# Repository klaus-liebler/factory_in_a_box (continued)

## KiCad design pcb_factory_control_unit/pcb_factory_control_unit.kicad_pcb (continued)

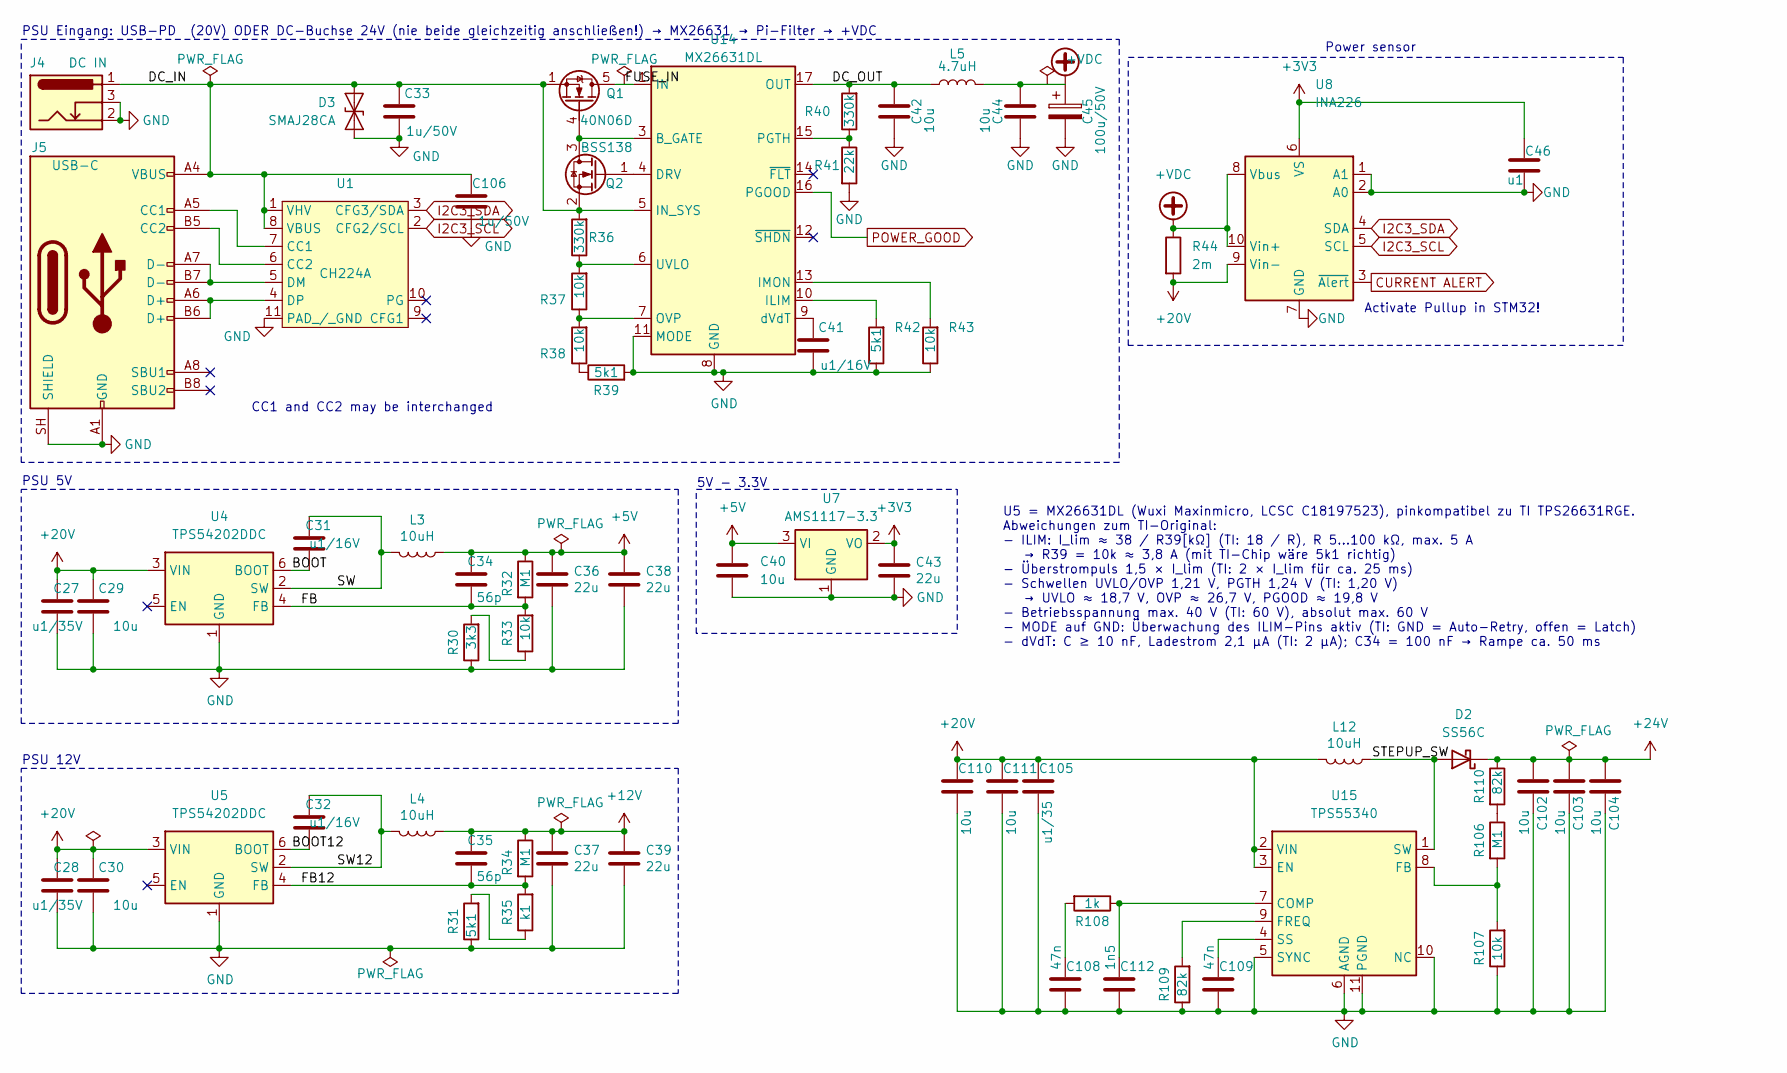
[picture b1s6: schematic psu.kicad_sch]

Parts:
C27, C28: u1/35V; C_0805_2012Metric; MPN CC0805KRX7R9BB104; LCSC C49678
C29, C30, C40, C110, C111: 10u; C_0805_2012Metric; MPN CGA0805X5R106K500MT; LCSC C6119889
C31, C32, C41: u1/16V; C_0402_1005Metric; MPN CL05B104KO5NNNC; LCSC C1525
C33, C106: 1u/50V; C_0805_2012Metric; MPN CL21B105KBFNNNE; LCSC C28323
C34, C35: 56p; C_0402_1005Metric; MPN CC0402JRNPO9BN560; LCSC C107007
C36, C37, C38, C39, C43: 22u; C_0805_2012Metric; MPN CL21A226MAQNNNE; LCSC C45783
C42, C44, C102, C103, C104: 10u; C_1210_3225Metric; MPN GRM32ER71H106KA12L; LCSC C77102
C45: 100u/50V; CP_Elec_8x10; MPN EEE-FK1H101P; LCSC C178548
C46: u1; C_0402_1005Metric; MPN CL05B104KO5NNNC; LCSC C1525
C105: u1/35; C_0805_2012Metric; MPN CC0805KRX7R9BB104; LCSC C49678
C108, C109: 47n; C_0402_1005Metric; MPN CL05B473KO5NNNC; LCSC C307434
C112: 1n5; C_0402_1005Metric; MPN CL05B152KB5NNNC; LCSC C23967
D2: SS56C; D_SMC; LCSC C24138
D3: SMAJ28CA; D_SMA; MPN SMAJ28CA; LCSC C19077546
J4: DC IN; BarrelJack_Horizontal; MPN DC-005 2.0
J5: USB-C; USB_C_Receptacle_HRO_TYPE-C-31-M-12_smaller; MPN TYPE-C-31-M-12; LCSC C165948
L3, L4, L12: 10uH; L_Abracon_ASPI-0630LR; MPN FXL0650-100-M; LCSC C475521
L5: 4.7uH; L_Bourns_SRP1245A; LCSC C54620181
Q1: 40N06D; VSON-8_3.3x3.3mm_P0.65mm_NexFET; MPN 40N06D; LCSC C7543836
Q2: BSS138; SOT-23; MPN BSS138LT1G; LCSC C82045
R30: 3k3; R_0402_1005Metric; MPN 0402WGF3301TCE; LCSC C25890
R31, R39, R42: 5k1; R_0402_1005Metric; MPN 0402WGF5101TCE; LCSC C25905
R32, R34, R106: M1; R_0402_1005Metric; MPN 0402WGF1003TCE; LCSC C25741
R33, R37, R38, R43, R107: 10k; R_0402_1005Metric; MPN 0402WGF1002TCE; LCSC C25744
R35: k1; R_0402_1005Metric; MPN 0402WGF1000TCE; LCSC C25076
R36, R40: 330k; R_0402_1005Metric; MPN 0402WGF3303TCE; LCSC C25778
R41: 22k; R_0402_1005Metric; MPN 0402WGF2202TCE; LCSC C25768
R44: 2m; R_1206_3216Metric; LCSC C844294
R108: 1k; R_0402_1005Metric; MPN 0402WGF1001TCE; LCSC C11702
R109, R110: 82k; R_0402_1005Metric; MPN 0402WGF8202TCE; LCSC C4142
U1: CH224A; Texas_DSQ0010A_WSON-10-1EP_2x2mm_P0.4mm_EP0.9x1.5mm_Thermal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; LCSC C42459160
U4, U5: TPS54202DDC; SOT-23-6; MPN TPS54202DDCR; LCSC C191884
U7: AMS1117-3.3; SOT-223-3_TabPin2; LCSC C6186
U8: INA226; TSSOP-10_3x3mm_P0.5mm; LCSC C49851
U14: MX26631DL; Texas_RGE0024H_VQFN-24-1EP_4x4mm_P0.5mm_EP2.7x2.7mm_Thermal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; MPN MX26631DL; LCSC C18197523
U15: TPS55340; WQFN-16-1EP_3x3mm_P0.5mm_EP1.68x1.68mm_ThermalVias; MPN TPS55340RTER; LCSC C169167

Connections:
+3V3: C43.1, C46.1, U7.2 (VO), U8.6 (VS); also elsewhere on the board
+5V: C34.2, C36.1, C38.1, C40.1, L3.1, R32.1, U7.3 (VI); also elsewhere on the board
+12V: C35.2, C37.1, C39.1, L4.1, R34.1; also elsewhere on the board
+20V: C27.2, C28.2, C29.2, C30.2, C105.2, C110.2, C111.2, L12.2, R44.2, U4.3 (VIN), U5.3 (VIN), U8.9 (Vin-), U15.2 (VIN), U15.3 (EN); also elsewhere on the board
+24V: C102.1, C103.1, C104.1, D2.1 (K), R110.1; also elsewhere on the board
+VDC: C44.1, C45.1, L5.2, R44.1, U8.8 (Vbus), U8.10 (Vin+)
/psu/BOOT: C31.1, U4.6 (BOOT)
/psu/BOOT12: C32.1, U5.6 (BOOT)
/psu/DC_IN: C33.2, C106.2, D3.2 (A2), J4.1, J5.A4 (VBUS), J5.A9 (VBUS), J5.B4 (VBUS), J5.B9 (VBUS), Q1.1 (S), Q1.2 (S), Q1.3 (S), Q2.2 (S), R36.2, U1.1 (VHV), U1.8 (VBUS), U14.5 (IN_SYS)
/psu/DC_OUT: C42.1, L5.1, R40.2, U14.17 (OUT), U14.18 (OUT)
/psu/FB: C34.1, R32.2, R33.2, U4.4 (FB)
/psu/FB12: C35.1, R34.2, R35.2, U5.4 (FB)
/psu/FUSE_IN: Q1.5 (D), U14.1 (IN), U14.2 (IN)
/psu/STEPUP_SW: D2.2 (A), L12.1, U15.1 (SW), U15.15 (SW), U15.16 (SW)
/psu/SW: C31.2, L3.2, U4.2 (SW)
/psu/SW12: C32.2, L4.2, U5.2 (SW)
CURRENT ALERT: U8.3 (~Alert); also elsewhere on the board
GND: C27.1, C28.1, C29.1, C30.1, C33.1, C36.2, C37.2, C38.2, C39.2, C40.2, C41.1, C42.2, C43.2, C44.2, C45.2, C46.2, C102.2, C103.2, C104.2, C105.1, C106.1, C108.1, C109.1, C110.1, C111.1, C112.1, D3.1 (A1), J4.2, J4.3, J5.A1 (GND), J5.A12 (GND), J5.B1 (GND), J5.B12 (GND), J5.SH (SHIELD), R30.1, R31.1, R39.2, R41.2, R42.1, R43.1, R107.1, R109.1, U1.11 (PAD_/_GND), U4.1 (GND), U5.1 (GND), U7.1 (GND), U8.1 (A1), U8.2 (A0), U8.7 (GND), U14.8 (GND), U14.11 (MODE), U14.25 (GND), U15.5 (SYNC), U15.6 (AGND), U15.10 (NC), U15.11 (PGND), U15.12 (PGND), U15.13 (PGND), U15.14 (NC), U15.17 (AGND); also elsewhere on the board
I2C3_SCL: U1.2 (CFG2/SCL), U8.5 (SCL); also elsewhere on the board
I2C3_SDA: U1.3 (CFG3/SDA), U8.4 (SDA); also elsewhere on the board
unnamed: C108.2, R108.2
unnamed: J5.A5 (CC1), U1.7 (CC1)
unnamed: J5.B5 (CC2), U1.6 (CC2)
unnamed: Q1.4 (G), Q2.3 (D), U14.3 (B_GATE)
unnamed: Q2.1 (G), U14.4 (DRV)
unnamed: R30.2, R33.1
unnamed: R31.2, R35.1
unnamed: R38.1, R39.1
unnamed: R106.1, R110.2
unnamed: J5.A7 (D-), J5.B7 (D-), U1.5 (DM)
unnamed: J5.A6 (D+), J5.B6 (D+), U1.4 (DP)
unnamed: R42.2, U14.10 (ILIM)
unnamed: R43.2, U14.13 (IMON)
unnamed: R37.1, R38.2, U14.7 (OVP)
unnamed: R40.1, R41.1, U14.15 (PGTH)
unnamed: R36.1, R37.2, U14.6 (UVLO)
unnamed: C41.2, U14.9 (dVdT)
unnamed: C112.2, R108.1, U15.7 (COMP)
unnamed: R106.2, R107.2, U15.8 (FB)
unnamed: R109.2, U15.9 (FREQ)
unnamed: C109.2, U15.4 (SS)
POWER_GOOD: U14.16 (PGOOD); also elsewhere on the board

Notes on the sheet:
PSU 5V
Power sensor
U5 = MX26631DL (Wuxi Maxinmicro, LCSC C18197523), pinkompatibel zu TI TPS26631RGE. Abweichungen zum TI-Original: - ILIM: I_lim ≈ 38 / R39[kΩ] (TI: 18 / R), R 5…100 kΩ, max. 5 A → R39 = 10k ≈ 3,8 A (mit TI-Chip wäre 5k1 richtig) - Überstrompuls 1,5 × I_lim (TI: 2 × I_lim für ca. 25 ms) - Schwellen U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
PSU Eingang: USB-PD (20V) ODER DC-Buchse 24V (nie beide gleichzeitig anschließen!) → MX26631 → Pi-Filter → +VDC
PSU 12V
Activate Pullup in STM32!
CC1 and CC2 may be interchanged
5V - 3.3V

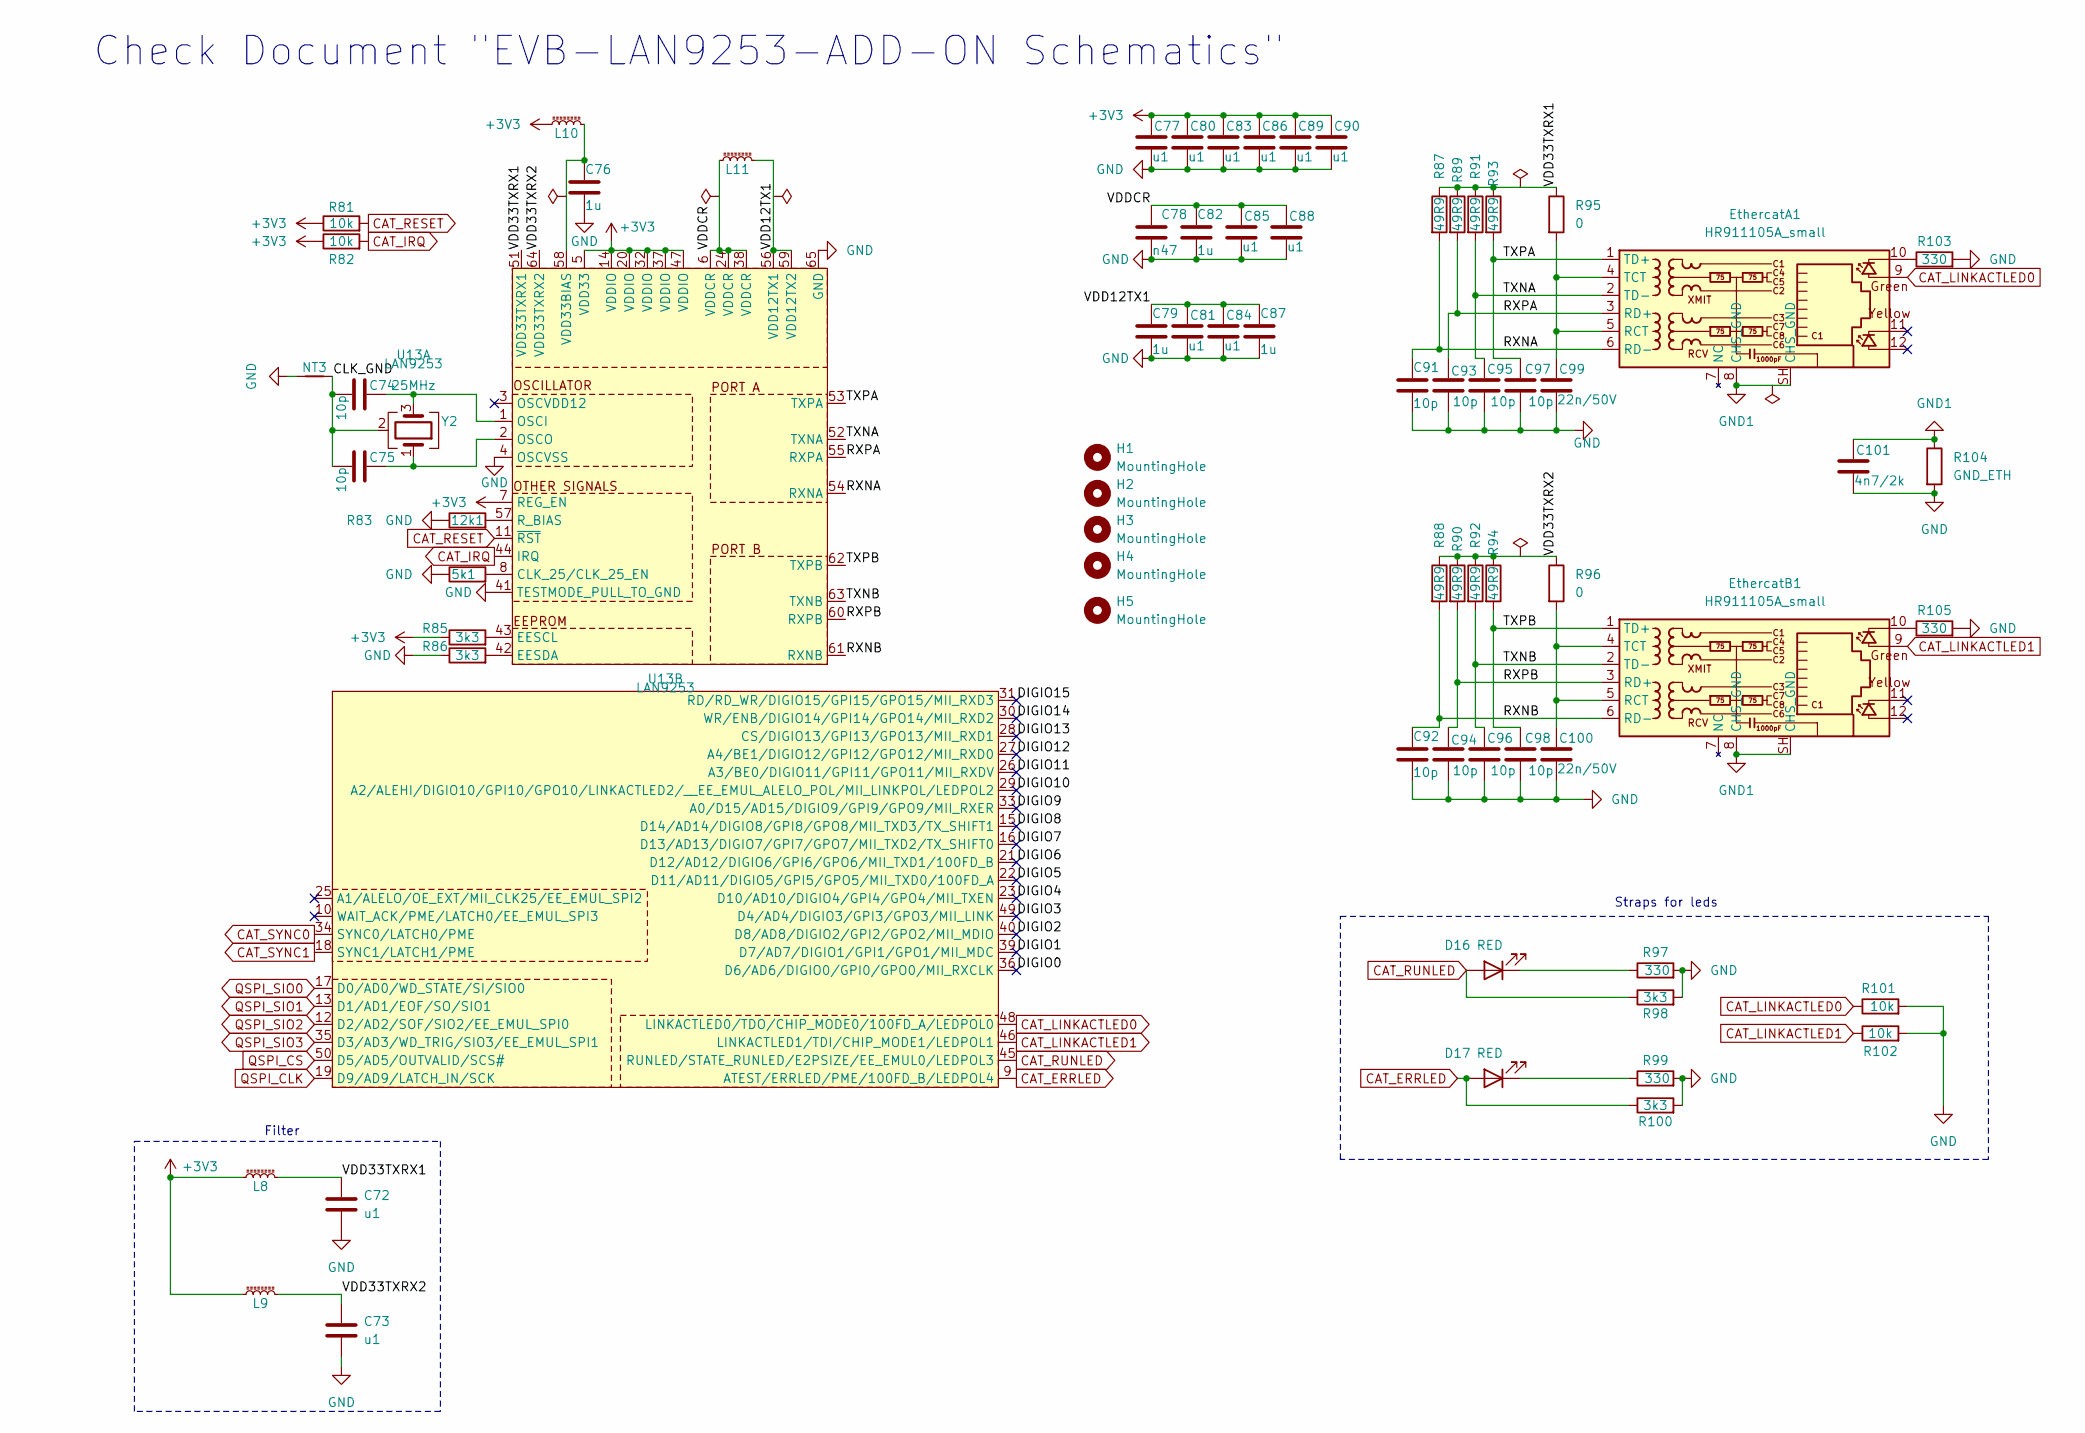
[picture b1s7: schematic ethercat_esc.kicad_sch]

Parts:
C72, C73, C77, C80, C81, C83, C84, C85, C86, C88, C89, C90: u1; C_0402_1005Metric; MPN CL05B104KO5NNNC; LCSC C1525
C74, C75, C91, C92, C93, C94, C95, C96, C97, C98: 10p; C_0402_1005Metric; MPN CC0402JRNPO9BN100; LCSC C106199
C76, C79, C82, C87: 1u; C_0402_1005Metric; MPN CL05A105KA5NQNC; LCSC C52923
C78: n47; C_0402_1005Metric; MPN GRM1555C1H471JA01D; LCSC C76971
C99, C100: 22n/50V; C_0402_1005Metric; MPN 0402B223K500NT; LCSC C1532
C101: 4n7/2k; C_0805_2012Metric_Pad1.18x1.45mm_HandSolder
D16, D17: RED; LED_1206_3216Metric_ReverseMount_Hole1.8x2.4mm; MPN P2-1206RTCS2-0.9T-F; LCSC C2827254
EthercatA1: HR911105A_small; RJ45_HANRUN_HR911105A; LCSC C12074
EthercatB1: HR911105A_small; RJ45_HANRUN_HR911105A; LCSC C12074
H1, H2, H3, H4: MountingHole; MountingHole_4.3mm_M4_DIN965
H5: MountingHole; barrel_jack_positive_polarity
L8, L9, L10, L11: 220R@100M; L_0603_1608Metric; MPN BLM18PG221SN1D; LCSC C80165
NT3: NetTie_2; NetTie-2_SMD_Pad0.5mm
R81, R82, R101, R102: 10k; R_0402_1005Metric; MPN 0402WGF1002TCE; LCSC C25744
R83: 12k1; R_0402_1005Metric; LCSC C25852
R84: 5k1; R_0402_1005Metric; MPN 0402WGF5101TCE; LCSC C25905
R85, R86, R98, R100: 3k3; R_0402_1005Metric; MPN 0402WGF3301TCE; LCSC C25890
R87, R88, R89, R90, R91, R92, R93, R94: 49R9; R_0402_1005Metric; LCSC C25120
R95, R96: 0; R_0805_2012Metric_Pad1.20x1.40mm_HandSolder; MPN 0805W8F0000T5E; LCSC C17477
R97, R99, R103, R105: 330; R_0402_1005Metric; MPN 0402WGF3300TCE; LCSC C25104
R104: GND_ETH; R_0805_2012Metric_Pad1.20x1.40mm_HandSolder
U13: LAN9253; QFN-64-1EP_9x9mm_P0.5mm_EP6x6mm_ThermalVias; MPN LAN9253-I/R4X; LCSC C5745149
Y2: 25MHz; Crystal_SMD_2016-4Pin_2.0x1.6mm; LCSC C19711739

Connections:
+3V3: C77.1, C80.1, C83.1, C86.1, C89.1, C90.1, L8.1, L9.1, L10.1, R81.1, R82.1, R85.1, U13.5 (VDD33), U13.7 (REG_EN), U13.14 (VDDIO), U13.20 (VDDIO), U13.32 (VDDIO), U13.37 (VDDIO), U13.47 (VDDIO); also elsewhere on the board
/EtherCAT/CLK_GND: C74.2, C75.2, NT3.2, Y2.2 (G), Y2.4 (G)
/EtherCAT/DIGIO0: U13.36 (D6/AD6/DIGIO0/GPI0/GPO0/MII_RXCLK)
/EtherCAT/DIGIO1: U13.39 (D7/AD7/DIGIO1/GPI1/GPO1/MII_MDC)
/EtherCAT/DIGIO2: U13.40 (D8/AD8/DIGIO2/GPI2/GPO2/MII_MDIO)
/EtherCAT/DIGIO3: U13.49 (D4/AD4/DIGIO3/GPI3/GPO3/MII_LINK)
/EtherCAT/DIGIO4: U13.23 (D10/AD10/DIGIO4/GPI4/GPO4/MII_TXEN)
/EtherCAT/DIGIO5: U13.22 (D11/AD11/DIGIO5/GPI5/GPO5/MII_TXD0/100F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)
/EtherCAT/DIGIO6: U13.21 (D12/AD12/DIGIO6/GPI6/GPO6/MII_TXD1/100F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)
/EtherCAT/DIGIO7: U13.16 (D13/AD13/DIGIO7/GPI7/GPO7/MII_TXD2/TX_S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)
/EtherCAT/DIGIO8: U13.15 (D14/AD14/DIGIO8/GPI8/GPO8/MII_TXD3/TX_S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)
/EtherCAT/DIGIO9: U13.33 (A0/D15/AD15/DIGIO9/GPI9/GPO9/MII_RXER)
/EtherCAT/DIGIO10: U13.29 (A2/ALEHI/DIGIO10/GPI10/GPO10/LINKACTLED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)
/EtherCAT/DIGIO11: U13.26 (A3/BE0/DIGIO11/GPI11/GPO11/MII_RXDV)
/EtherCAT/DIGIO12: U13.27 (A4/BE1/DIGIO12/GPI12/GPO12/MII_RXD0)
/EtherCAT/DIGIO13: U13.28 (CS/DIGIO13/GPI13/GPO13/MII_RXD1)
/EtherCAT/DIGIO14: U13.30 (WR/ENB/DIGIO14/GPI14/GPO14/MII_RXD2)
/EtherCAT/DIGIO15: U13.31 (RD/RD_WR/DIGIO15/GPI15/GPO15/MII_RXD3)
/EtherCAT/RXNA: C91.1, EthercatA1.6 (RD-), R87.2, U13.54 (RXNA)
/EtherCAT/RXNB: C92.1, EthercatB1.6 (RD-), R88.2, U13.61 (RXNB)
/EtherCAT/RXPA: C93.1, EthercatA1.3 (RD+), R89.2, U13.55 (RXPA)
/EtherCAT/RXPB: C94.1, EthercatB1.3 (RD+), R90.2, U13.60 (RXPB)
/EtherCAT/TXNA: C95.1, EthercatA1.2 (TD-), R91.2, U13.52 (TXNA)
/EtherCAT/TXNB: C96.1, EthercatB1.2 (TD-), R92.2, U13.63 (TXNB)
/EtherCAT/TXPA: C97.1, EthercatA1.1 (TD+), R93.2, U13.53 (TXPA)
/EtherCAT/TXPB: C98.1, EthercatB1.1 (TD+), R94.2, U13.62 (TXPB)
/EtherCAT/VDD12TX1: C79.1, C81.1, C84.1, C87.1, L11.2, U13.56 (VDD12TX1), U13.59 (VDD12TX2)
/EtherCAT/VDD33TXRX1: C72.1, L8.2, R87.1, R89.1, R91.1, R93.1, R95.1, U13.51 (VDD33TXRX1)
/EtherCAT/VDD33TXRX2: C73.1, L9.2, R88.1, R90.1, R92.1, R94.1, R96.1, U13.64 (VDD33TXRX2)
/EtherCAT/VDDCR: C78.1, C82.1, C85.1, C88.1, L11.1, U13.6 (VDDCR), U13.24 (VDDCR), U13.38 (VDDCR)
CAT_ERRLED: D17.2 (A), R100.1, U13.9 (ATEST/ERRLED/PME/100FD_B/LEDPOL4)
CAT_IRQ: R82.2, U13.44 (IRQ); also elsewhere on the board
CAT_LINKACTLED0: EthercatA1.9, R101.1, U13.48 (LINKACTLED0/TDO/CHIP_MODE0/100FD_A/LEDP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)
CAT_LINKACTLED1: EthercatB1.9, R102.1, U13.46 (LINKACTLED1/TDI/CHIP_MODE1/LEDPOL1)
CAT_RESET: R81.2, U13.11 (~RST); also elsewhere on the board
CAT_RUNLED: D16.2 (A), R98.1, U13.45 (RUNLED/STATE_RUNLED/E2PSIZE/EE_EMUL0/LE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)
CAT_SYNC0: U13.34 (SYNC0/LATCH0/PME); also elsewhere on the board
CAT_SYNC1: U13.18 (SYNC1/LATCH1/PME); also elsewhere on the board
GND: C72.2, C73.2, C76.2, C77.2, C78.2, C79.2, C80.2, C81.2, C82.2, C83.2, C84.2, C85.2, C86.2, C87.2, C88.2, C89.2, C90.2, C91.2, C92.2, C93.2, C94.2, C95.2, C96.2, C97.2, C98.2, C99.2, C100.2, C101.2, NT3.1, R83.1, R84.1, R86.1, R97.2, R98.2, R99.2, R100.2, R101.2, R102.2, R103.2, R104.2, R105.2, U13.4 (OSCVSS), U13.41 (TESTMODE_PULL_TO_GND), U13.65 (GND); also elsewhere on the board
GND1: C101.1, EthercatA1.8 (CHS_GND), EthercatA1.SH (CHS_GND), EthercatB1.8 (CHS_GND), EthercatB1.SH (CHS_GND), R104.1; also elsewhere on the board
unnamed: D16.1 (K), R97.1
unnamed: D17.1 (K), R99.1
unnamed: EthercatA1.10, R103.1
unnamed: C99.1, EthercatA1.4 (TCT), EthercatA1.5 (RCT), R95.2
unnamed: EthercatB1.10, R105.1
unnamed: C100.1, EthercatB1.4 (TCT), EthercatB1.5 (RCT), R96.2
unnamed: R84.2, U13.8 (CLK_25/CLK_25_EN)
unnamed: R85.2, U13.43 (EESCL)
unnamed: R86.2, U13.42 (EESDA)
unnamed: C74.1, U13.1 (OSCI), Y2.3
unnamed: C75.1, U13.2 (OSCO), Y2.1
unnamed: R83.2, U13.57 (R_BIAS)
unnamed: C76.1, L10.2, U13.58 (VDD33BIAS)
QSPI_CLK: U13.19 (D9/AD9/LATCH_IN/SCK); also elsewhere on the board
QSPI_CS: U13.50 (D5/AD5/OUTVALID/SCS#); also elsewhere on the board
QSPI_SIO0: U13.17 (D0/AD0/WD_STATE/SI/SIO0); also elsewhere on the board
QSPI_SIO1: U13.13 (D1/AD1/EOF/SO/SIO1); also elsewhere on the board
QSPI_SIO2: U13.12 (D2/AD2/SOF/SIO2/EE_EMUL_SPI0); also elsewhere on the board
QSPI_SIO3: U13.35 (D3/AD3/WD_TRIG/SIO3/EE_EMUL_SPI1); also elsewhere on the board

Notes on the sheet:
Straps for leds
Filter
Check Document "EVB-LAN9253-ADD-ON Schematics"

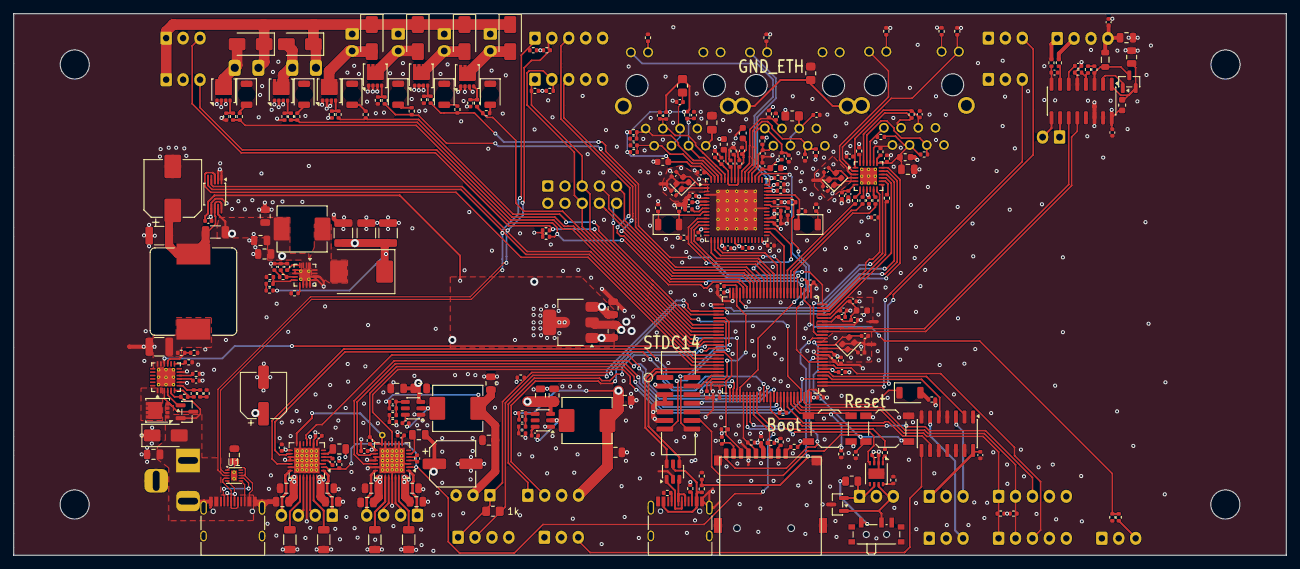
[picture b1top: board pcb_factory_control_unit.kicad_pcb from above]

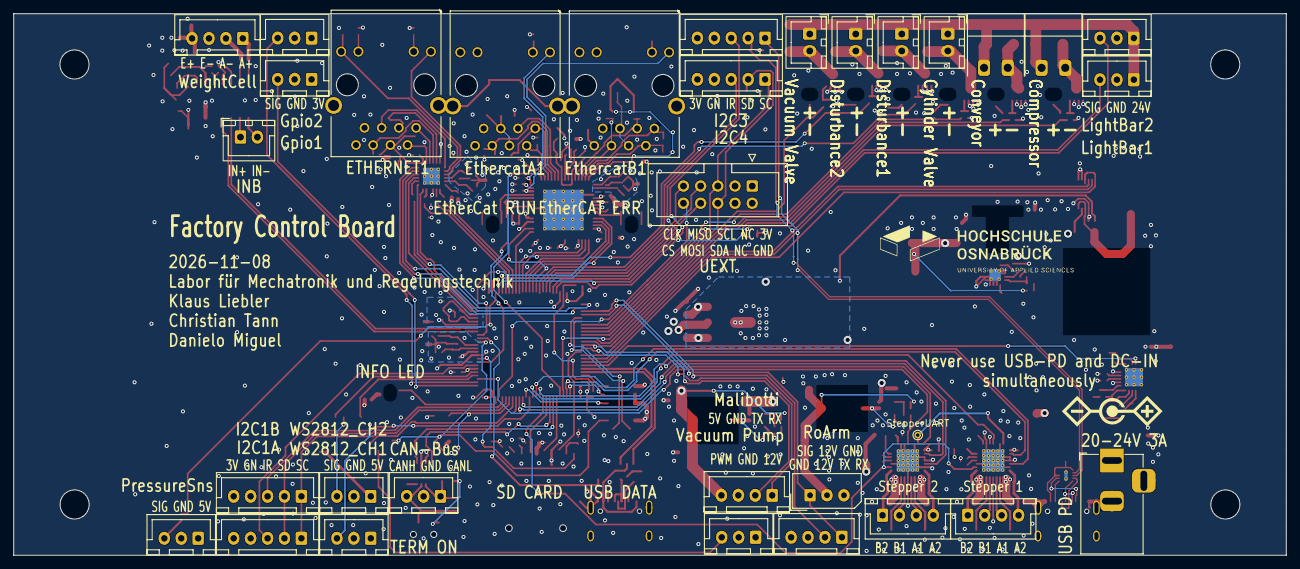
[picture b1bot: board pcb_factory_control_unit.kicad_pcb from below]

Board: 4 copper layers, 188.0 x 80.0 mm, 333 parts (33 on the bottom side), 244 nets.

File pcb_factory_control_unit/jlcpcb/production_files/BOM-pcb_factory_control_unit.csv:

Comment,Designator,Footprint,LCSC,Quantity
0,"R95,R96",R_0805_2012Metric_Pad1.20x1.40mm_HandSolder,C17477,2
100m,"R49,R50,R51,R52",R_1206_3216Metric,C7467250,4
100u/50V,C45,CP_Elec_8x10,C178548,1
100uF,"C64,C65",CP_Elec_6.3x7.7,C72478,2
10k,"R10,R101,R102,R107,R11,R113,R114,R116,R118,R12,R14,R15,R16,R24,R33,R37,R38,R43,R47,R48,R54,R55,R57,R78,R79,R8,R81,R82,R9",R_0402_1005Metric,C25744,29
10n,"C19,C23,C24",C_0402_1005Metric,C5137480,3
10p,"C107,C113,C18,C20,C74,C75,C91,C92,C93,C94,C95,C96,C97,C98",C_0402_1005Metric,C106199,14
10u,"C110,C111,C25,C29,C30,C40,C67,C69",C_0805_2012Metric,C6119889,8
10u,"C102,C103,C104,C42,C44",C_1210_3225Metric,C77102,5
10uH,"L12,L3,L4",L_Abracon_ASPI-0630LR,C475521,3
12k1,"R22,R83",R_0402_1005Metric,C25852,2
1k,"R1,R108,R13,R53,R58,R61,R62,R63,R64,R70,R71",R_0402_1005Metric,C11702,11
1n5,C112,C_0402_1005Metric,C23967,1
1u,"C14,C21,C4,C76,C79,C82,C87",C_0402_1005Metric,C52923,7
1u/50V,"C106,C33",C_0805_2012Metric,C28323,2
220R@100M,"L1,L10,L11,L2,L7,L8,L9",L_0603_1608Metric,C80165,7
22k,R41,R_0402_1005Metric,C25768,1
22n/50V,"C100,C26,C56,C58,C99",C_0402_1005Metric,C1532,5
22u,"C36,C37,C38,C39,C43",C_0805_2012Metric,C45783,5
22u/35V,"C59,C60,C61,C62",C_0805_2012Metric,C6119901,4
25MHz,"Y1,Y2,Y3",Crystal_SMD_2016-4Pin_2.0x1.6mm,C19711739,3
2m,R44,R_1206_3216Metric,C844294,1
2u2,"C13,C15,C55,C57",C_0402_1005Metric,C12530,4
330,"R103,R105,R28,R29,R97,R99",R_0402_1005Metric,C25104,6
330k,"R36,R40",R_0402_1005Metric,C25778,2
33R,"R17,R18,R19,R21",R_0402_1005Metric,C25105,4
3k3,"R100,R20,R30,R80,R85,R86,R98",R_0402_1005Metric,C25890,7
3u3,L6,L_0805_2012Metric,C162585,1
4.7uH,L5,L_Bourns_SRP1245A,C212263,1
40N06D,"Q1,Q10,Q4,Q5,Q6,Q7,Q8",VSON-8_3.3x3.3mm_P0.65mm_NexFET,C7543836,7
47n,"C108,C109",C_0402_1005Metric,C307434,2
49R9,"R23,R25,R26,R27,R87,R88,R89,R90,R91,R92,R93,R94",R_0402_1005Metric,C25120,12
4u7,C11,C_0402_1005Metric,C307423,1
56p,"C34,C35",C_0402_1005Metric,C107007,2
5k1,"R2,R3,R31,R39,R4,R42,R45,R46,R5,R6,R7,R84",R_0402_1005Metric,C25905,12
74AHCT125,U11,SOIC-14_3.9x8.7mm_P1.27mm,C155176,1
82k,"R109,R110",R_0402_1005Metric,C4142,2
AMS1117-3.3,U7,SOT-223-3_TabPin2,C6186,1
BSS138,Q2,SOT-23,C82045,1
CH224A,U1,Texas_DSQ0010A_WSON-10-1EP_2x2mm_P0.4mm_EP0.9x1.5mm_ThermalVias,C42459160,1
HR911105A_small,"ETHERNET1,EthercatA1,EthercatB1",RJ45_HANRUN_HR911105A,C12074,3
HX711,U12,SOIC-16_3.9x9.9mm_P1.27mm,C6705483,1
INA226,U8,TSSOP-10_3x3mm_P0.5mm,C49851,1
LAN8742A,U3,VQFN-24-1EP_4x4mm_P0.5mm_EP2.5x2.5mm_ThermalVias,C621425,1
LAN9253,U13,QFN-64-1EP_9x9mm_P0.5mm_EP6x6mm_ThermalVias,C5745149,1
M1,"R106,R32,R34,R60,R65,R67,R69,R73,R75",R_0402_1005Metric,C25741,9
MX26631DL,U14,Texas_RGE0024H_VQFN-24-1EP_4x4mm_P0.5mm_EP2.7x2.7mm_ThermalVias,C18197523,1
Micro_SD_Card_Det1,J3,microSD push,C381082,1
NUP2105L,D18,SOT-23,C2976509,1
OFF TERM  ON,SW3,SW_SPDT_PCM12,C221841,1
Push,"SW1,SW2",SW_SPST_TL3342_smaller,C318884,2
RED,"D1,D12,D13,D16,D17,D4,D5,D6,D7",LED_1206_3216Metric_ReverseMount_Hole1.8x2.4mm,C2827254,9
S8550,Q9,SOT-23,C364313,1
SIT3051TK,U2,DFN-8-1EP_3x3mm_P0.65mm_EP1.55x2.4mm,C601078,1
SMAJ28CA,D3,D_SMA,C19077546,1
SS34,"D10,D11,D14,D15,D8,D9",D_SMA,C8678,6
SS56C,D2,D_SMC,C24138,1
STDC14,J2,IDC-Header_2x07_P1.27mm_Vertical_SMD,C6332251,1
STM32H743VITx,U17,LQFP-100_14x14mm_P0.5mm,C114409,1
TMC2209,"U10,U9",QFN-28-1EP_5x5mm_P0.5mm_EP3.75x3.75mm_ThermalVias,C2150710,2
TPS54202DDC,"U4,U5",SOT-23-6,C191884,2
TPS55340,U15,WQFN-16-1EP_3x3mm_P0.5mm_EP1.68x1.68mm_ThermalVias,C169167,1
USB-C,"J5,J6",USB_C_Receptacle_HRO_TYPE-C-31-M-12_smaller,C165948,2
USBLC6-2SC6,U16,SOT-23-6,C2687116,1
k1,"R35,R59,R66,R68,R72,R74,R76,R77",R_0402_1005Metric,C25076,8
k12,R115,R_0805_2012Metric,C17437,1
n47,"C22,C78",C_0402_1005Metric,C76971,2
u1,"C1,C12,C16,C17,C2,C3,C46,C49,C5,C50,C6,C63,C66,C68,C7,C70,C71,C72,C73,C77,C8,C80,C81,C83,C84,C85,C86,C88,C89,C9,C90",C_0402_1005Metric,C1525,31
u1/16V,"C31,C32,C41",C_0402_1005Metric,C1525,3
u1/35,C105,C_0805_2012Metric,C49678,1
u1/35V,"C27,C28,C51,C52,C53,C54",C_0805_2012Metric,C49678,6
u1/50V,"C47,C48",C_0805_2012Metric,C49678,2
GND_ETH,R104,R_0805_2012Metric_Pad1.20x1.40mm_HandSolder,,1
4n7/2k,C101,C_0805_2012Metric_Pad1.18x1.45mm_HandSolder,,1
INB,J28,JST_XH_B2B-XH-A_1x02_P2.50mm_Vertical,,1
Gpio1,J30,JST_XH_B3B-XH-A_1x03_P2.50mm_Vertical_smaller,,1
I2C1A,J9,JST_XH_B5B-XH-A_1x05_P2.50mm_Vertical_smaller,,1
Vacuum Valve,J25,JST_XH_B2B-XH-A_1x02_P2.50mm_Vertical,,1
Gpio2,J31,JST_XH_B3B-XH-A_1x03_P2.50mm_Vertical_smaller,,1
I2C3,J7,JST_XH_B5B-XH-A_1x05_P2.50mm_Vertical_smaller,,1
I2C1B,J8,JST_XH_B5B-XH-A_1x05_P2.50mm_Vertical_smaller,,1
Conveyor,J23,"PhoenixContact_MC_1,5_2-G-3.5_1x02_P3.50mm_Horizontal_smallerCourtyard",,1
Elevator,J17,JST_XH_B4B-XH-A_1x04_P2.50mm_Vertical_smaller,,1
RoArm,J20,Molex_SPOX_5267-03A_1x03_P2.50mm_Vertical,,1
Malibotti,J16,JST_XH_B4B-XH-A_1x04_P2.50mm_Vertical_smaller,,1
Disturbance1,J26,JST_XH_B2B-XH-A_1x02_P2.50mm_Vertical,,1
Weight,J29,JST_XH_B4B-XH-A_1x04_P2.50mm_Vertical_smaller,,1
StepperUART,TP4,TestPoint_THTPad_D1.0mm_Drill0.5mm,,1
I2C4,IJ1,JST_XH_B5B-XH-A_1x05_P2.50mm_Vertical_smaller,,1
UEXT,J15,IDC-Header_2x05_P2.54mm_Vertical,,1
Cylinder Valve,J21,JST_XH_B2B-XH-A_1x02_P2.50mm_Vertical,,1
DC IN,J4,BarrelJack_Horizontal,,1
PressureSns,J14,JST_XH_B3B-XH-A_1x03_P2.50mm_Vertical_smaller,,1
WS2812_CH1,J10,JST_XH_B3B-XH-A_1x03_P2.50mm_Vertical_smaller,,1
WS2812_CH2,J11,JST_XH_B3B-XH-A_1x03_P2.50mm_Vertical_smaller,,1
Vacuum Pump,J19,JST_XH_B3B-XH-A_1x03_P2.50mm_Vertical_smaller,,1
Disturbance2,J27,JST_XH_B2B-XH-A_1x02_P2.50mm_Vertical,,1
RoArm,J22,JST_XH_B4B-XH-A_1x04_P2.50mm_Vertical_smaller,,1
Compressor,J24,"PhoenixContact_MC_1,5_2-G-3.5_1x02_P3.50mm_Horizontal_smallerCourtyard",,1
Sorter,J18,JST_XH_B4B-XH-A_1x04_P2.50mm_Vertical_smaller,,1
LightBar2,J13,JST_XH_B3B-XH-A_1x03_P2.50mm_Vertical_smaller,,1
LightBar1,J12,JST_XH_B3B-XH-A_1x03_P2.50mm_Vertical_smaller,,1
CAN-Bus,J1,JST_XH_B3B-XH-A_1x03_P2.50mm_Vertical_smaller,,1
